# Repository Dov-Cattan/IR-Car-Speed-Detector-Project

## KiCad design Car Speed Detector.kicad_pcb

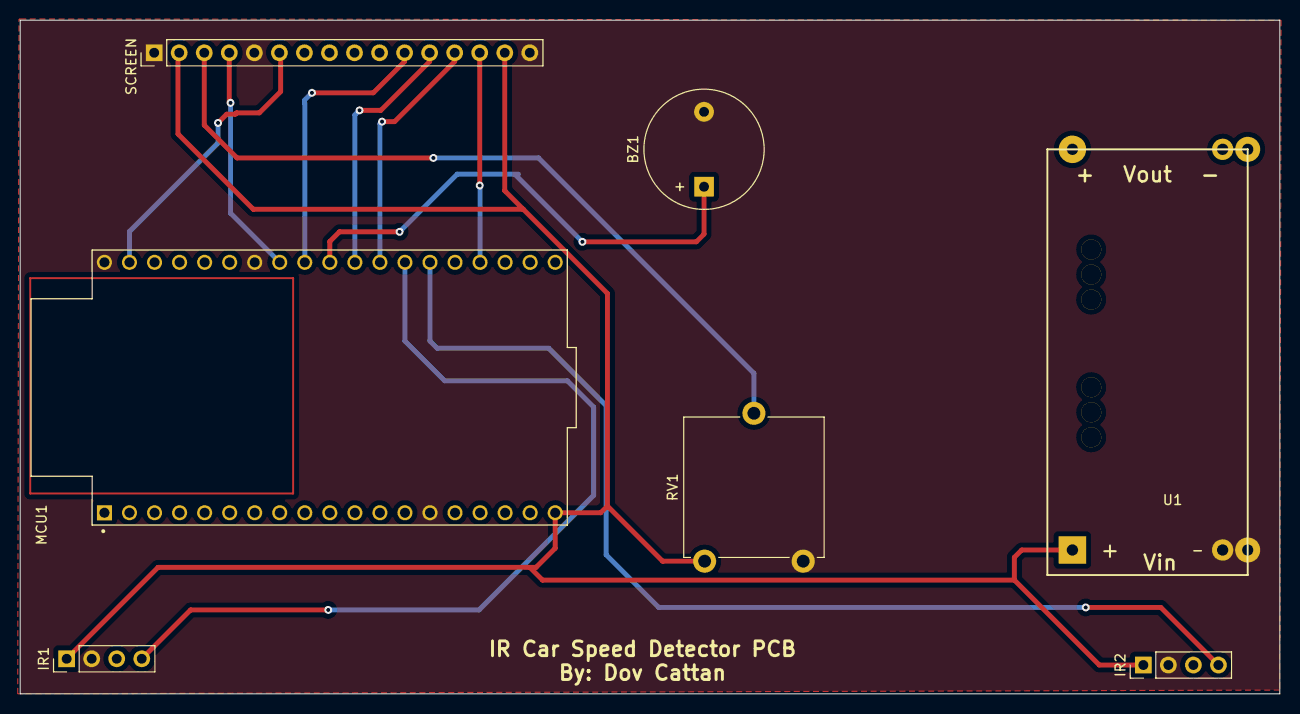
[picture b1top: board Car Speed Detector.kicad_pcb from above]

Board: 2 copper layers, 127.8 x 68.3 mm, 7 parts (0 on the bottom side), 12 nets.

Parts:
BZ1: Buzzer; Buzzer_12x9.5RM7.6
IR1, IR2: Conn_01x04; PinHeader_1x04_P2.54mm_Vertical
MCU1: ESP32-DEVKITC; MODULE_ESP32-DEVKITC
RV1: R_Potentiometer; Potentiometer_ACP_CA14V-15_Vertical
SCREEN: Conn_01x16; PinHeader_1x16_P2.54mm_Vertical
U1: BUCK CONVERTER; DD_3amp-w_pot_holes

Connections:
/0: IR2.4, MCU1.25 (IO0)
/4: IR1.4, MCU1.26 (IO4)
/5: BZ1.1 (-), MCU1.29 (IO5)
/5V: IR1.1, IR2.1, MCU1.19 (EXT_5V), RV1.3, SCREEN.2, SCREEN.15, U1.1
/15: MCU1.23 (IO15), SCREEN.14
/16: MCU1.27 (IO16), SCREEN.13
/17: MCU1.28 (IO17), SCREEN.12
/18: MCU1.30 (IO18), SCREEN.11
/19: MCU1.31 (IO19), SCREEN.4
/23: MCU1.37 (IO23), SCREEN.6
/V0: RV1.2, SCREEN.3
GND: BZ1.2 (+), IR1.2, IR2.2, MCU1.14 (GND1), MCU1.32 (GND2), MCU1.38 (GND3), RV1.1, SCREEN.1, SCREEN.5, SCREEN.16, U1.2
